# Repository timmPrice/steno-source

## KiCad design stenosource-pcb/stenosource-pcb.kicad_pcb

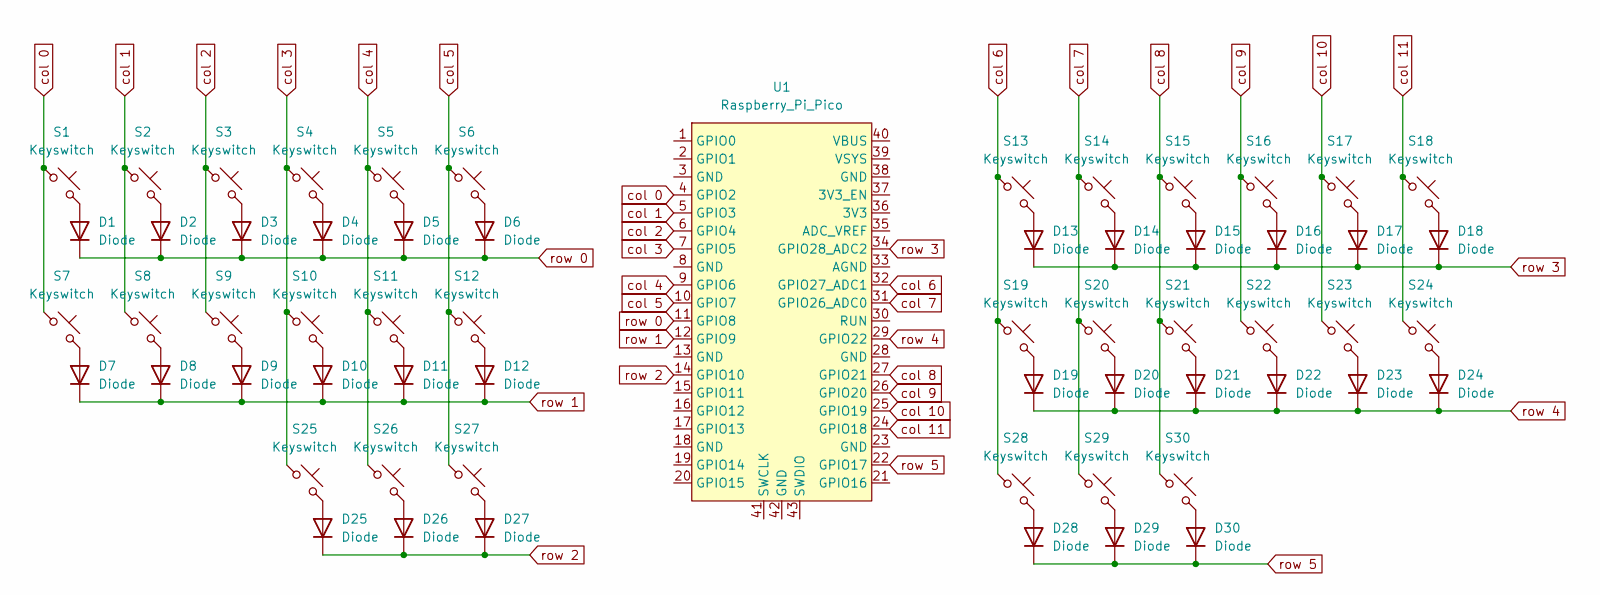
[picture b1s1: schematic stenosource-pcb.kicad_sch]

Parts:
D1, D2, D3, D4, D5, D6, D7, D8, D9, D10, D11, D12, D13, D14, D15, D16, D17, D18, D19, D20, D21, D22, D23, D24, D25, D26, D27, D28, D29, D30: Diode; Diode_DO-35
S1, S2, S3, S4, S5, S6, S7, S8, S9, S10, S11, S12, S13, S14, S15, S16, S17, S18, S19, S20, S21, S22, S23, S24, S25, S26, S27, S28, S29, S30: Keyswitch; MX_PCB_1.00u
U1: Raspberry_Pi_Pico

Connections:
unnamed: D1.2 (A), S1.2
unnamed: D2.2 (A), S2.2
unnamed: D3.2 (A), S3.2
unnamed: D4.2 (A), S4.2
unnamed: D5.2 (A), S5.2
unnamed: D6.2 (A), S6.2
unnamed: D7.2 (A), S7.2
unnamed: D8.2 (A), S8.2
unnamed: D9.2 (A), S9.2
unnamed: D10.2 (A), S10.2
unnamed: D11.2 (A), S11.2
unnamed: D12.2 (A), S12.2
unnamed: D13.2 (A), S13.2
unnamed: D14.2 (A), S14.2
unnamed: D15.2 (A), S15.2
unnamed: D16.2 (A), S16.2
unnamed: D17.2 (A), S17.2
unnamed: D18.2 (A), S18.2
unnamed: D19.2 (A), S19.2
unnamed: D20.2 (A), S20.2
unnamed: D21.2 (A), S21.2
unnamed: D22.2 (A), S22.2
unnamed: D23.2 (A), S23.2
unnamed: D24.2 (A), S24.2
unnamed: D25.2 (A), S25.2
unnamed: D26.2 (A), S26.2
unnamed: D27.2 (A), S27.2
unnamed: D28.2 (A), S28.2
unnamed: D29.2 (A), S29.2
unnamed: D30.2 (A), S30.2
col 0: S1.1, S7.1, U1.4 (GPIO2)
col 1: S2.1, S8.1, U1.5 (GPIO3)
col 2: S3.1, S9.1, U1.6 (GPIO4)
col 3: S4.1, S10.1, S25.1, U1.7 (GPIO5)
col 4: S5.1, S11.1, S26.1, U1.9 (GPIO6)
col 5: S6.1, S12.1, S27.1, U1.10 (GPIO7)
col 6: S13.1, S19.1, S28.1, U1.32 (GPIO27_ADC1)
col 7: S14.1, S20.1, S29.1, U1.31 (GPIO26_ADC0)
col 8: S15.1, S21.1, S30.1, U1.27 (GPIO21)
col 9: S16.1, S22.1, U1.26 (GPIO20)
col 10: S17.1, S23.1, U1.25 (GPIO19)
col 11: S18.1, S24.1, U1.24 (GPIO18)
row 0: D1.1 (K), D2.1 (K), D3.1 (K), D4.1 (K), D5.1 (K), D6.1 (K), U1.11 (GPIO8)
row 1: D7.1 (K), D8.1 (K), D9.1 (K), D10.1 (K), D11.1 (K), D12.1 (K), U1.12 (GPIO9)
row 2: D25.1 (K), D26.1 (K), D27.1 (K), U1.14 (GPIO10)
row 3: D13.1 (K), D14.1 (K), D15.1 (K), D16.1 (K), D17.1 (K), D18.1 (K), U1.34 (GPIO28_ADC2)
row 4: D19.1 (K), D20.1 (K), D21.1 (K), D22.1 (K), D23.1 (K), D24.1 (K), U1.29 (GPIO22)
row 5: D28.1 (K), D29.1 (K), D30.1 (K), U1.22 (GPIO17)

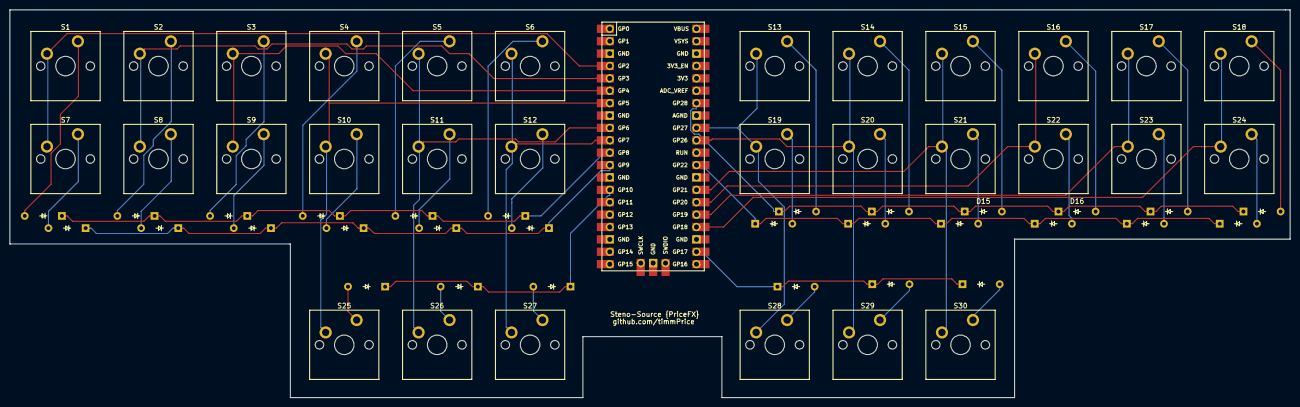
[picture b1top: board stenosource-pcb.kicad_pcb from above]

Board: 2 copper layers, 262.5 x 79.5 mm, 61 parts (0 on the bottom side), 48 nets.

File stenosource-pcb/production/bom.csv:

Designator,Footprint,Quantity,Value,LCSC Part #
"D1, D10, D11, D12, D13, D14, D15, D16, D17, D18, D19, D2, D20, D21, D22, D23, D24, D25, D26, D27, D28, D29, D3, D30, D4, D5, D6, D7, D8, D9",Diode_DO-35,30,Diode,
"S1, S10, S11, S12, S13, S14, S15, S16, S17, S18, S19, S2, S20, S21, S22, S23, S24, S25, S26, S27, S28, S29, S3, S30, S4, S5, S6, S7, S8, S9",MX_PCB_1.00u,30,Keyswitch,
U1,Raspberry_Pi_Pico,1,Raspberry_Pi_Pico,

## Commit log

2024-09-06 This is a split stenography keyboard layout with extra keys
2024-09-09 unsplit version
2024-09-12 pcb for stenosource keyboard (2x12_3)
2024-09-12 images of 'ss' pcb and schematic
2024-09-12 adding extra layer onto stenosource keymap
